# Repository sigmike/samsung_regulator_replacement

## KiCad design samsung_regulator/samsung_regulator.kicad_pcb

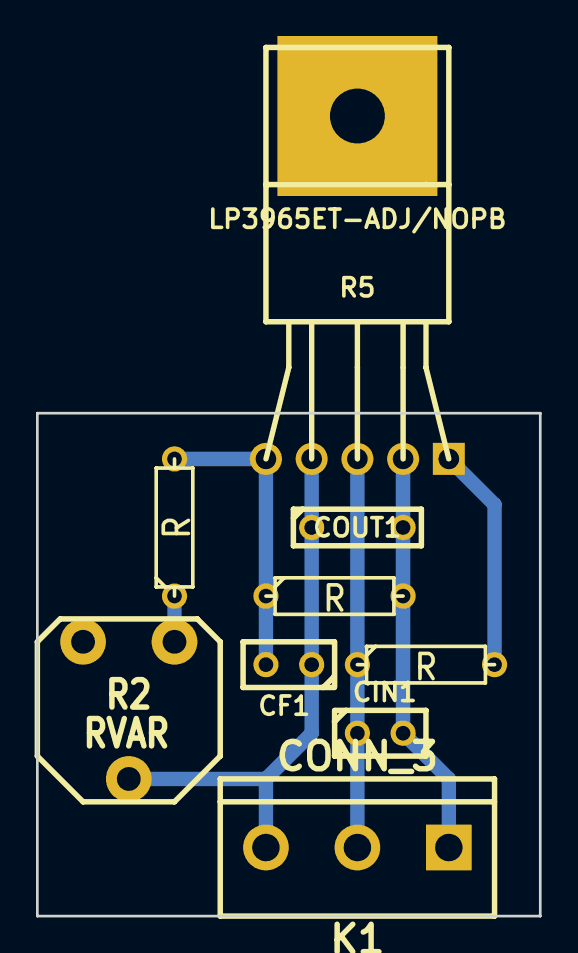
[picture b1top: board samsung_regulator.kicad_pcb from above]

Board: 2 copper layers, 27.9 x 27.9 mm, 9 parts (0 on the bottom side), 6 nets.

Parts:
CF1: C; C1
CIN1: C; C1
COUT1: C; C2
K1: CONN_3; bornier3
R1, R3, R4: R; R3
R2: RVAR
R5: LP3965ET-ADJ/NOPB; TO220-5

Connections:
GND: CIN1.2, COUT1.2, K1.1, R1.2, R5.3
unnamed: R2.2, R3.1
unnamed: R4.2, R5.1
unnamed: CF1.1, COUT1.1, K1.3, R2.1, R5.4
unnamed: CF1.2, R1.1, R3.2, R5.5
unnamed: CIN1.1, K1.2, R4.1, R5.2

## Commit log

2014-09-01 started lib
2014-09-15 started pcb
2014-11-03 connected all
2014-11-03 repositioned all
2014-11-03 linked
2014-11-16 thinker tracks
2014-11-16 more compact
2014-11-16 removed extra design in module
2014-11-16 named nets
2014-11-16 removed temp files
2014-11-16 imported img2mod
2014-11-16 imported previous img2mod version
2014-11-16 added logos
